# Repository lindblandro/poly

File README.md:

poly
====

A repository for the documentation of a school project.

Compiling
=========

To compile the file doc.tex into doc.pdf use pdflatex inside documentation/. 
  Linux:
    > pdflatex doc.tex 
  Windows (MikTeX+bash):
    > pdflatex.exe doc.tex

Images
======

Images are placed inside documentation/img/ as pdf files. Preferably
only vector graphics. To create vector graphics use e.g. Inkscape
and/or Dia. The former is extremely flexible graphics software with
somewhat steep learning curve and the latter is good mainly for
creating diagrams and is kind of an open source version of Office
Visio.

Source Code
===========

All the source code should go in source/ in a proper, descriptive
subdirectory.

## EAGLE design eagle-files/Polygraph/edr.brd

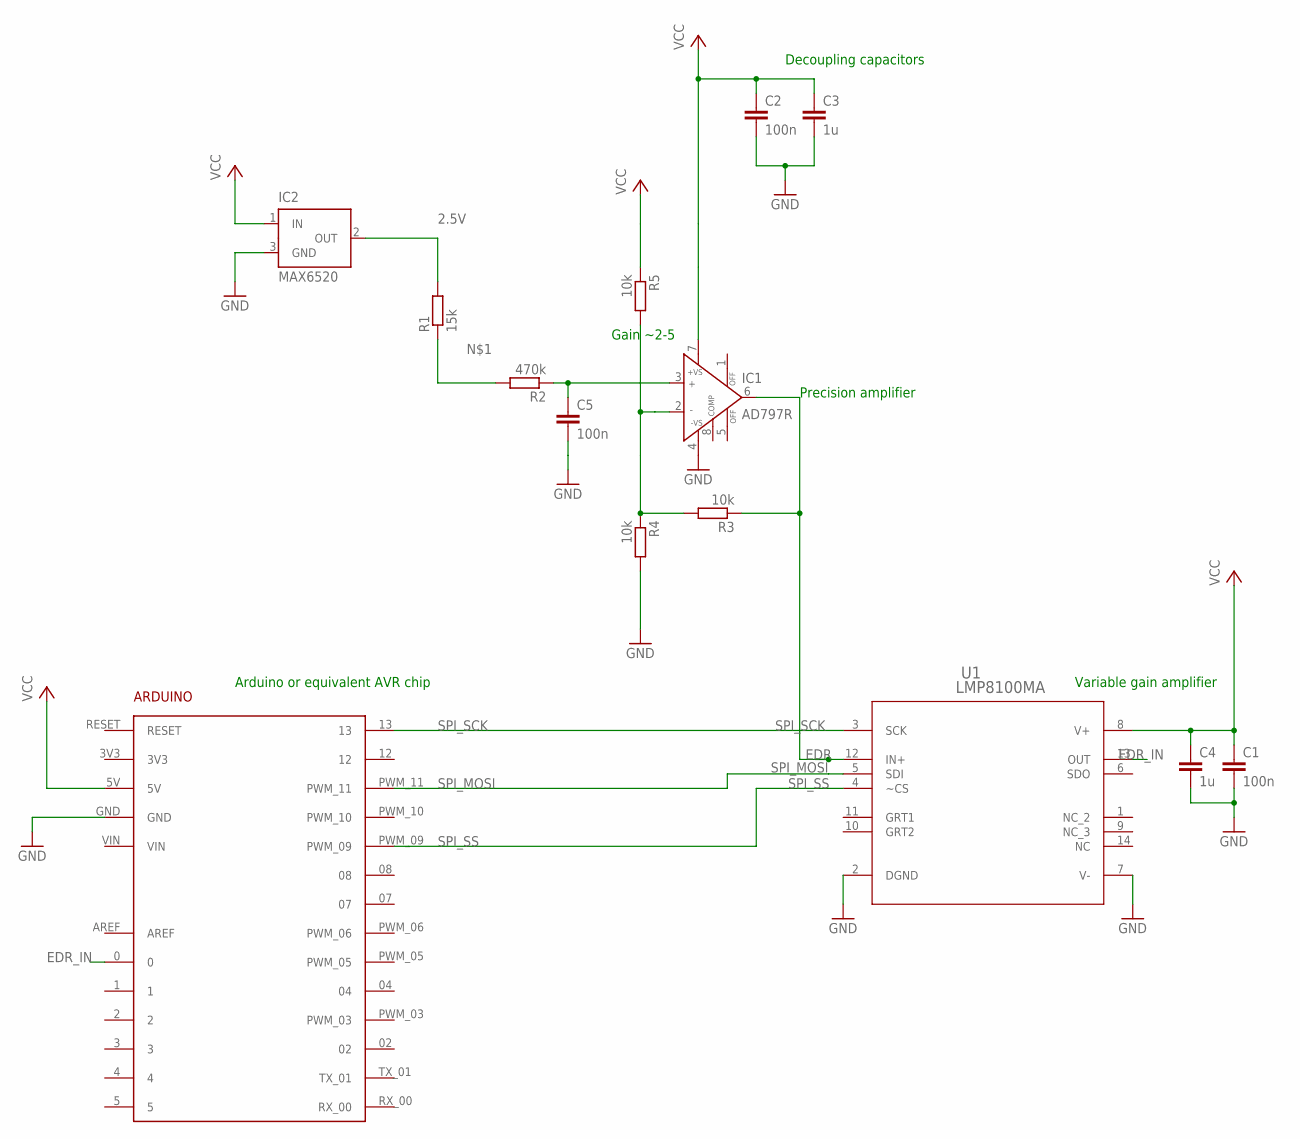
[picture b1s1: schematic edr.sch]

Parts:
ARDUINO1: ARDUINO2
C1, C2, C5: 100n; C0603
C3, C4: 1u; C0805
IC1: AD797R; SO8
IC2: MAX6520; SOT23
R1: 15k; R0603
R2: 470k; R0603
R3, R4, R5: 10k; R0603
U1: LMP8100MA; M14A

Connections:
2.5V: IC2.2 (OUT), R1.2
EDR: IC1.6 (OUT), R3.1, U1.12 (IN+)
EDR_IN: ARDUINO1.0, U1.13 (OUT)
GND: ARDUINO1.GND, C1.2, C2.2, C3.2, C4.2, C5.2, IC1.4 (-VS), IC2.3 (GND), R4.2, U1.2 (DGND), U1.7 (V-)
unnamed: R1.1, R2.2
unnamed: C5.1, IC1.3 (IN+), R2.1
unnamed: IC1.2 (IN-), R3.2, R4.1, R5.2
SPI_MOSI: ARDUINO1.PWM_11, U1.5 (SDI)
SPI_SCK: ARDUINO1.13, U1.3 (SCK)
SPI_SS: ARDUINO1.PWM_09, U1.4 (~CS)
VCC: ARDUINO1.5V, C1.1, C2.1, C3.1, C4.1, IC1.7 (+VS), IC2.1 (IN), R5.1, U1.8 (V+)

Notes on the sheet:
Decoupling capacitors
Precision amplifier
Variable gain amplifier
Arduino or equivalent AVR chip
Gain ~2-5

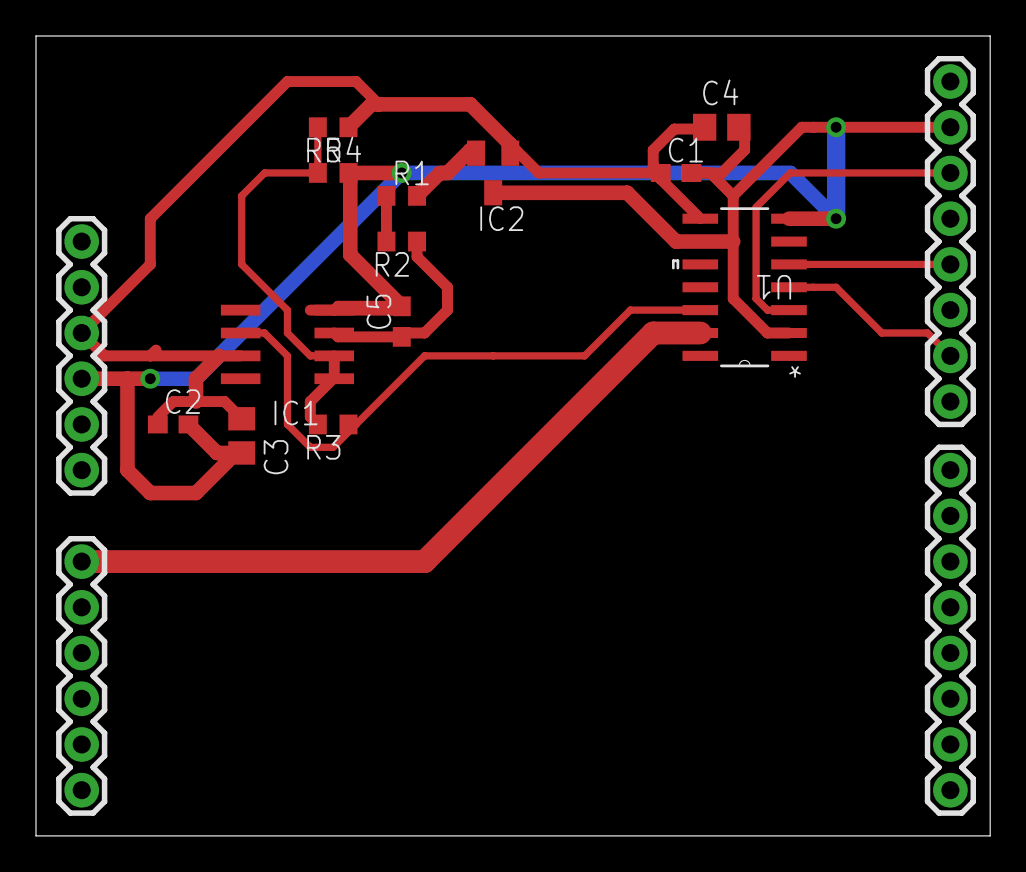
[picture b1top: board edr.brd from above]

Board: 2 copper layers, 53.0 x 44.4 mm, 14 parts (0 on the bottom side), 11 nets.

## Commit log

2012-06-17 Initial import of the documentation template. To add documentation, edit documentation/doc.tex. To compile, use pdflatex doc.tex in documentation/. Images are located in documentation/img/ as pdf fil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
2012-06-17 Added instructions.
2012-06-17 Added instructions about source code placement.
2012-06-18 First version of the Arduino firmware.
2012-06-18 Indendation fixed.
2012-06-18 The amplifier gain is an integer between 1 and 16. Changed integer types to reflect the witdth of the number.
2012-06-20 Eagle schematic and board layout. Lacks connector for the EDR and other sensors.
2012-09-05 The initial (for real) gain controller for the LMP8100.
2013-04-30 Added docs and datasheets and some labview code.
2013-04-30 Newest version of eagle files.
